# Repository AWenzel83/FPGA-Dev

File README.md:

# FPGA-Dev
Design and Supportfiles for the FPGA-Dev-Board used in the FPGA-Classes at the HS-Wismar

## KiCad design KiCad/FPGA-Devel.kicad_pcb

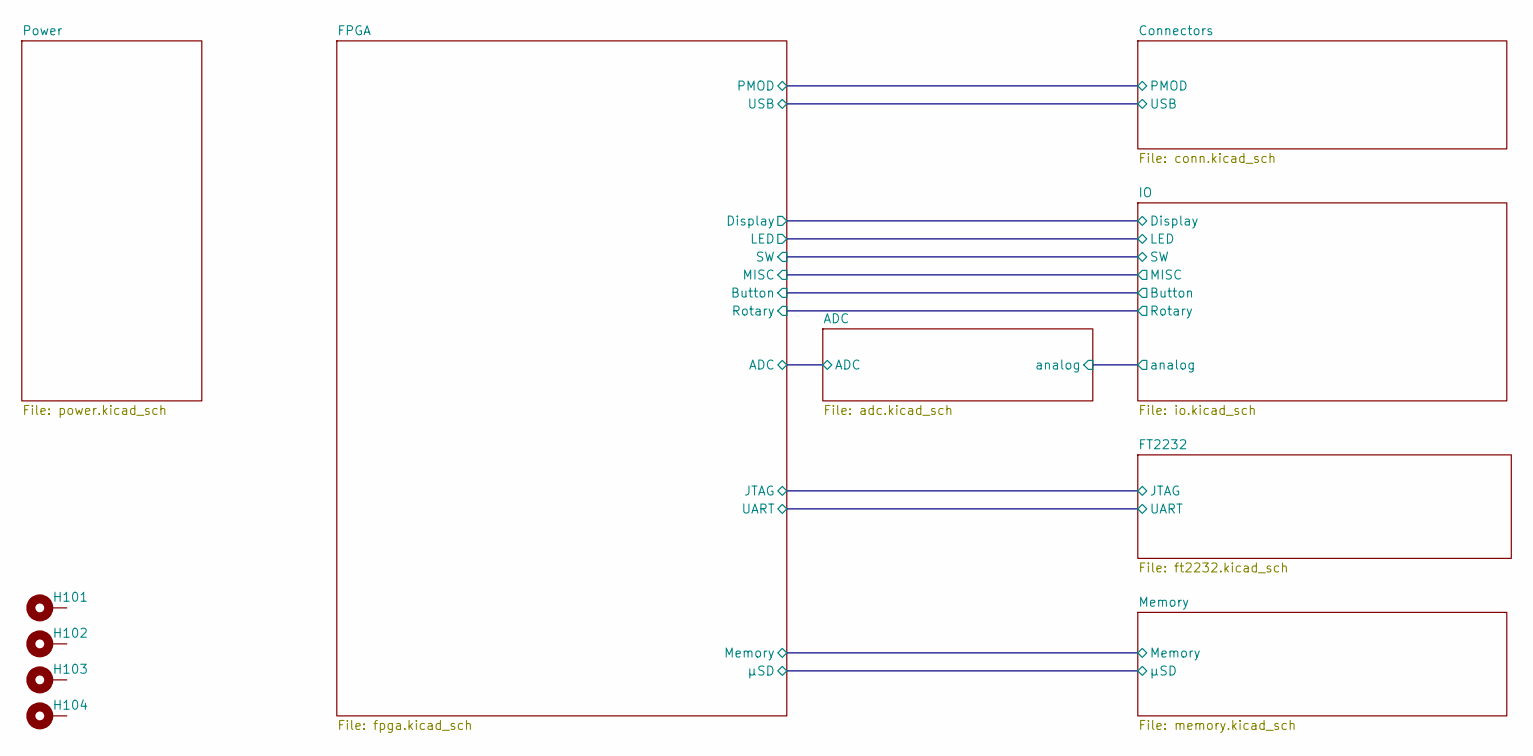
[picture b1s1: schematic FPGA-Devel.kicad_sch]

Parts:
H101, H102, H103, H104: MountingHole_Pad; MountingHole_3.2mm_M3_Pad_Via

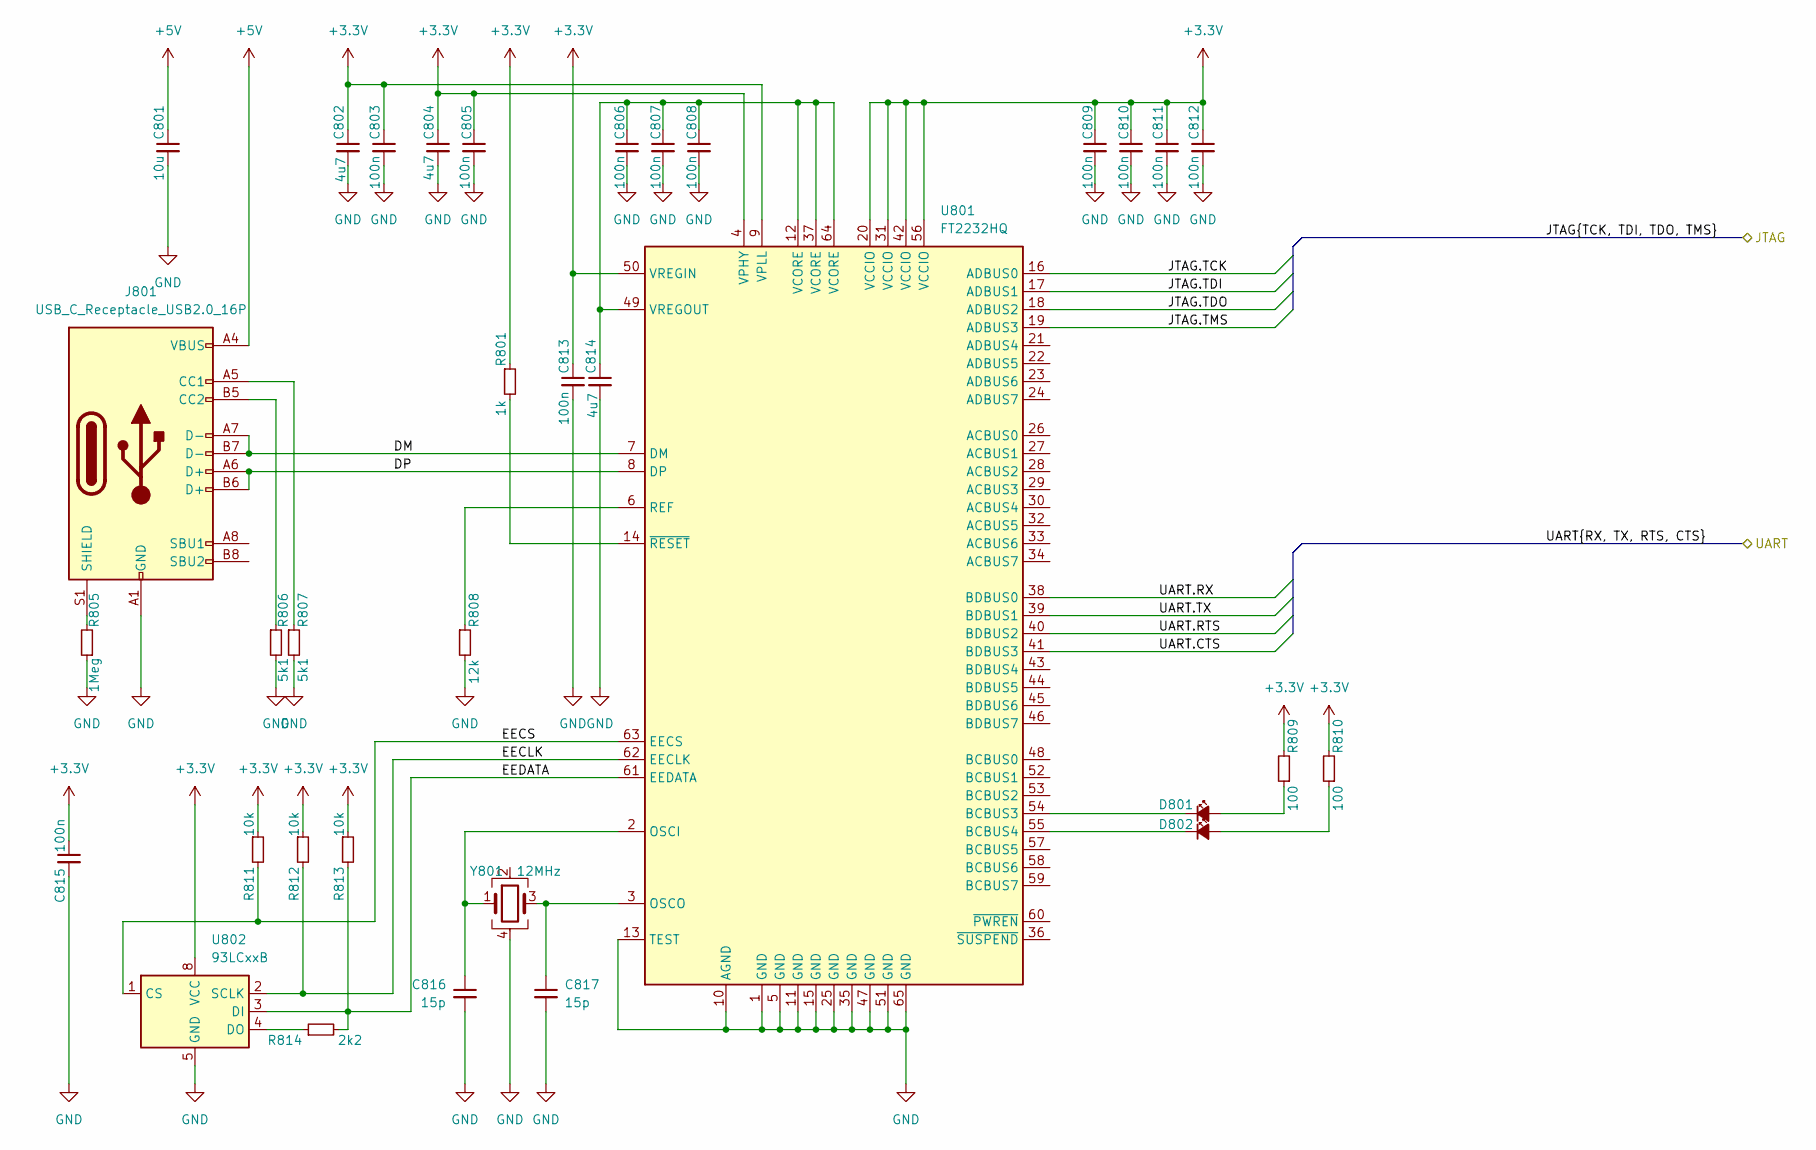
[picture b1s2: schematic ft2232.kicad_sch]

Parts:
C801: 10u; C_1206_3216Metric
C802, C804, C814: 4u7; C_0603_1608Metric
C803, C805, C806, C807, C808, C809, C810, C811, C812, C813, C815: 100n; C_0402_1005Metric
C816, C817: 15p; C_0402_1005Metric
D801, D802: LED_Small_Filled; LED_0603_1608Metric
J801: USB_C_Receptacle_USB2.0_16P; USB_C_Combo
R801: 1k; R_0402_1005Metric
R805: 1Meg; R_0402_1005Metric
R806, R807: 5k1; R_0402_1005Metric
R808: 12k; R_0402_1005Metric
R809, R810: 100; R_0402_1005Metric
R811, R812, R813: 10k; R_0402_1005Metric
R814: 2k2; R_0402_1005Metric
U801: FT2232HQ; QFN-64-1EP_9x9mm_P0.5mm_EP4.35x4.35mm
U802: 93LCxxB; SOIC-8_3.9x4.9mm_P1.27mm
Y801: 12MHz; Oscillator_SMD_Abracon_ASE-4Pin_3.2x2.5mm

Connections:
+3.3V: C802.1, C803.1, C804.1, C805.1, C809.1, C810.1, C811.1, C812.1, C813.1, C815.1, R801.1, R809.2, R810.2, R811.1, R812.1, R813.1, U801.4 (VPHY), U801.9 (VPLL), U801.20 (VCCIO), U801.31 (VCCIO), U801.42 (VCCIO), U801.50 (VREGIN), U801.56 (VCCIO), U802.8 (VCC); also elsewhere on the board
+5V: C801.1, J801.A4 (VBUS), J801.A9 (VBUS), J801.B4 (VBUS), J801.B9 (VBUS); also elsewhere on the board
/FT2232/DM: J801.A7 (D-), J801.B7 (D-), U801.7 (DM)
/FT2232/DP: J801.A6 (D+), J801.B6 (D+), U801.8 (DP)
/FT2232/EECLK: R812.2, U801.62 (EECLK), U802.2 (SCLK)
/FT2232/EECS: R811.2, U801.63 (EECS), U802.1 (CS)
/FT2232/EEDATA: R813.2, R814.2, U801.61 (EEDATA), U802.3 (DI)
/FT2232/JTAG.TCK: U801.16 (ADBUS0); also elsewhere on the board
/FT2232/JTAG.TDI: U801.17 (ADBUS1); also elsewhere on the board
/FT2232/JTAG.TDO: U801.18 (ADBUS2); also elsewhere on the board
/FT2232/JTAG.TMS: U801.19 (ADBUS3); also elsewhere on the board
/FT2232/UART.CTS: U801.41 (BDBUS3); also elsewhere on the board
/FT2232/UART.RTS: U801.40 (BDBUS2); also elsewhere on the board
/FT2232/UART.RX: U801.38 (BDBUS0); also elsewhere on the board
/FT2232/UART.TX: U801.39 (BDBUS1); also elsewhere on the board
GND: C801.2, C802.2, C803.2, C804.2, C805.2, C806.2, C807.2, C808.2, C809.2, C810.2, C811.2, C812.2, C813.2, C814.2, C815.2, C816.2, C817.2, J801.A1 (GND), J801.A12 (GND), J801.B1 (GND), J801.B12 (GND), R805.1, R806.2, R807.2, R808.2, U801.1 (GND), U801.5 (GND), U801.10 (AGND), U801.11 (GND), U801.13 (TEST), U801.15 (GND), U801.25 (GND), U801.35 (GND), U801.47 (GND), U801.51 (GND), U801.65 (GND), U802.5 (GND), Y801.4; also elsewhere on the board
unnamed: D801.2 (A), R809.1
unnamed: D801.1 (K), U801.54 (BCBUS3)
unnamed: D802.2 (A), R810.1
unnamed: D802.1 (K), U801.55 (BCBUS4)
unnamed: J801.A5 (CC1), R807.1
unnamed: J801.B5 (CC2), R806.1
unnamed: J801.S1 (SHIELD), R805.2
unnamed: C816.1, U801.2 (OSCI), Y801.1
unnamed: C817.1, U801.3 (OSCO), Y801.3
unnamed: R808.1, U801.6 (REF)
unnamed: C806.1, C807.1, C808.1, C814.1, U801.12 (VCORE), U801.37 (VCORE), U801.49 (VREGOUT), U801.64 (VCORE)
unnamed: R801.2, U801.14 (~RESET)
unnamed: R814.1, U802.4 (DO)

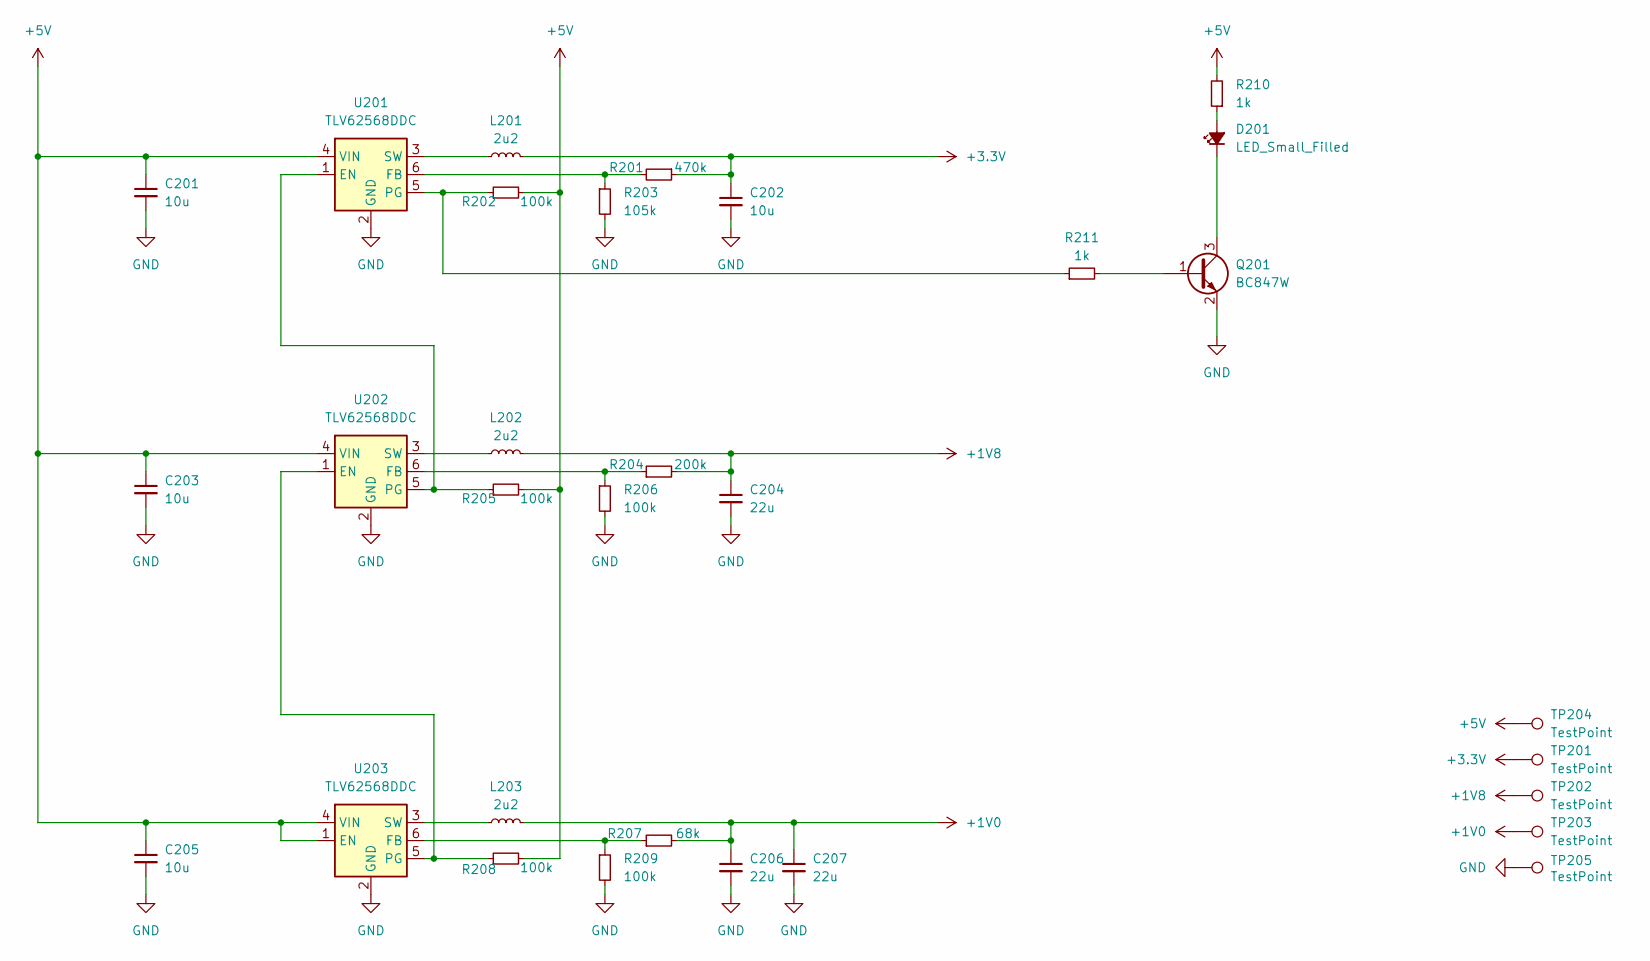
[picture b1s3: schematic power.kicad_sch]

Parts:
C201, C202, C203, C205: 10u; C_1206_3216Metric
C204, C206, C207: 22u; C_1206_3216Metric
D201: LED_Small_Filled; LED_0603_1608Metric
L201, L202, L203: 2u2; L_Bourns-SRN4018
Q201: BC847W; SOT-23-3
R201: 470k; R_0402_1005Metric
R202, R205, R206, R208, R209: 100k; R_0402_1005Metric
R203: 105k; R_0402_1005Metric
R204: 200k; R_0402_1005Metric
R207: 68k; R_0402_1005Metric
R210, R211: 1k; R_0402_1005Metric
TP201, TP202, TP203, TP204, TP205: TestPoint; TestPoint_THTPad_D2.0mm_Drill1.0mm
U201, U202, U203: TLV62568DDC; SOT-23-6

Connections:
+1V0: C206.1, C207.1, L203.2, R207.2, TP203.1 (1_1); also elsewhere on the board
+1V8: C204.1, L202.2, R204.2, TP202.1 (1_1); also elsewhere on the board
+3.3V: C202.1, L201.2, R201.1, TP201.1 (1_1); also elsewhere on the board
+5V: C201.1, C203.1, C205.1, R202.2, R205.2, R208.2, R210.2, TP204.1 (1_1), U201.4 (VIN), U202.4 (VIN), U203.1 (EN), U203.4 (VIN); also elsewhere on the board
GND: C201.2, C202.2, C203.2, C204.2, C205.2, C206.2, C207.2, Q201.2 (E), R203.2, R206.2, R209.2, TP205.1 (1_1), U201.2 (GND), U202.2 (GND), U203.2 (GND); also elsewhere on the board
unnamed: D201.2 (A), R210.1
unnamed: D201.1 (K), Q201.3 (C)
unnamed: Q201.1 (B), R211.2
unnamed: R205.1, U201.1 (EN), U202.5 (PG)
unnamed: R201.2, R203.1, U201.6 (FB)
unnamed: R202.1, R211.1, U201.5 (PG)
unnamed: L201.1, U201.3 (SW)
unnamed: R208.1, U202.1 (EN), U203.5 (PG)
unnamed: R204.1, R206.1, U202.6 (FB)
unnamed: L202.1, U202.3 (SW)
unnamed: R207.1, R209.1, U203.6 (FB)
unnamed: L203.1, U203.3 (SW)

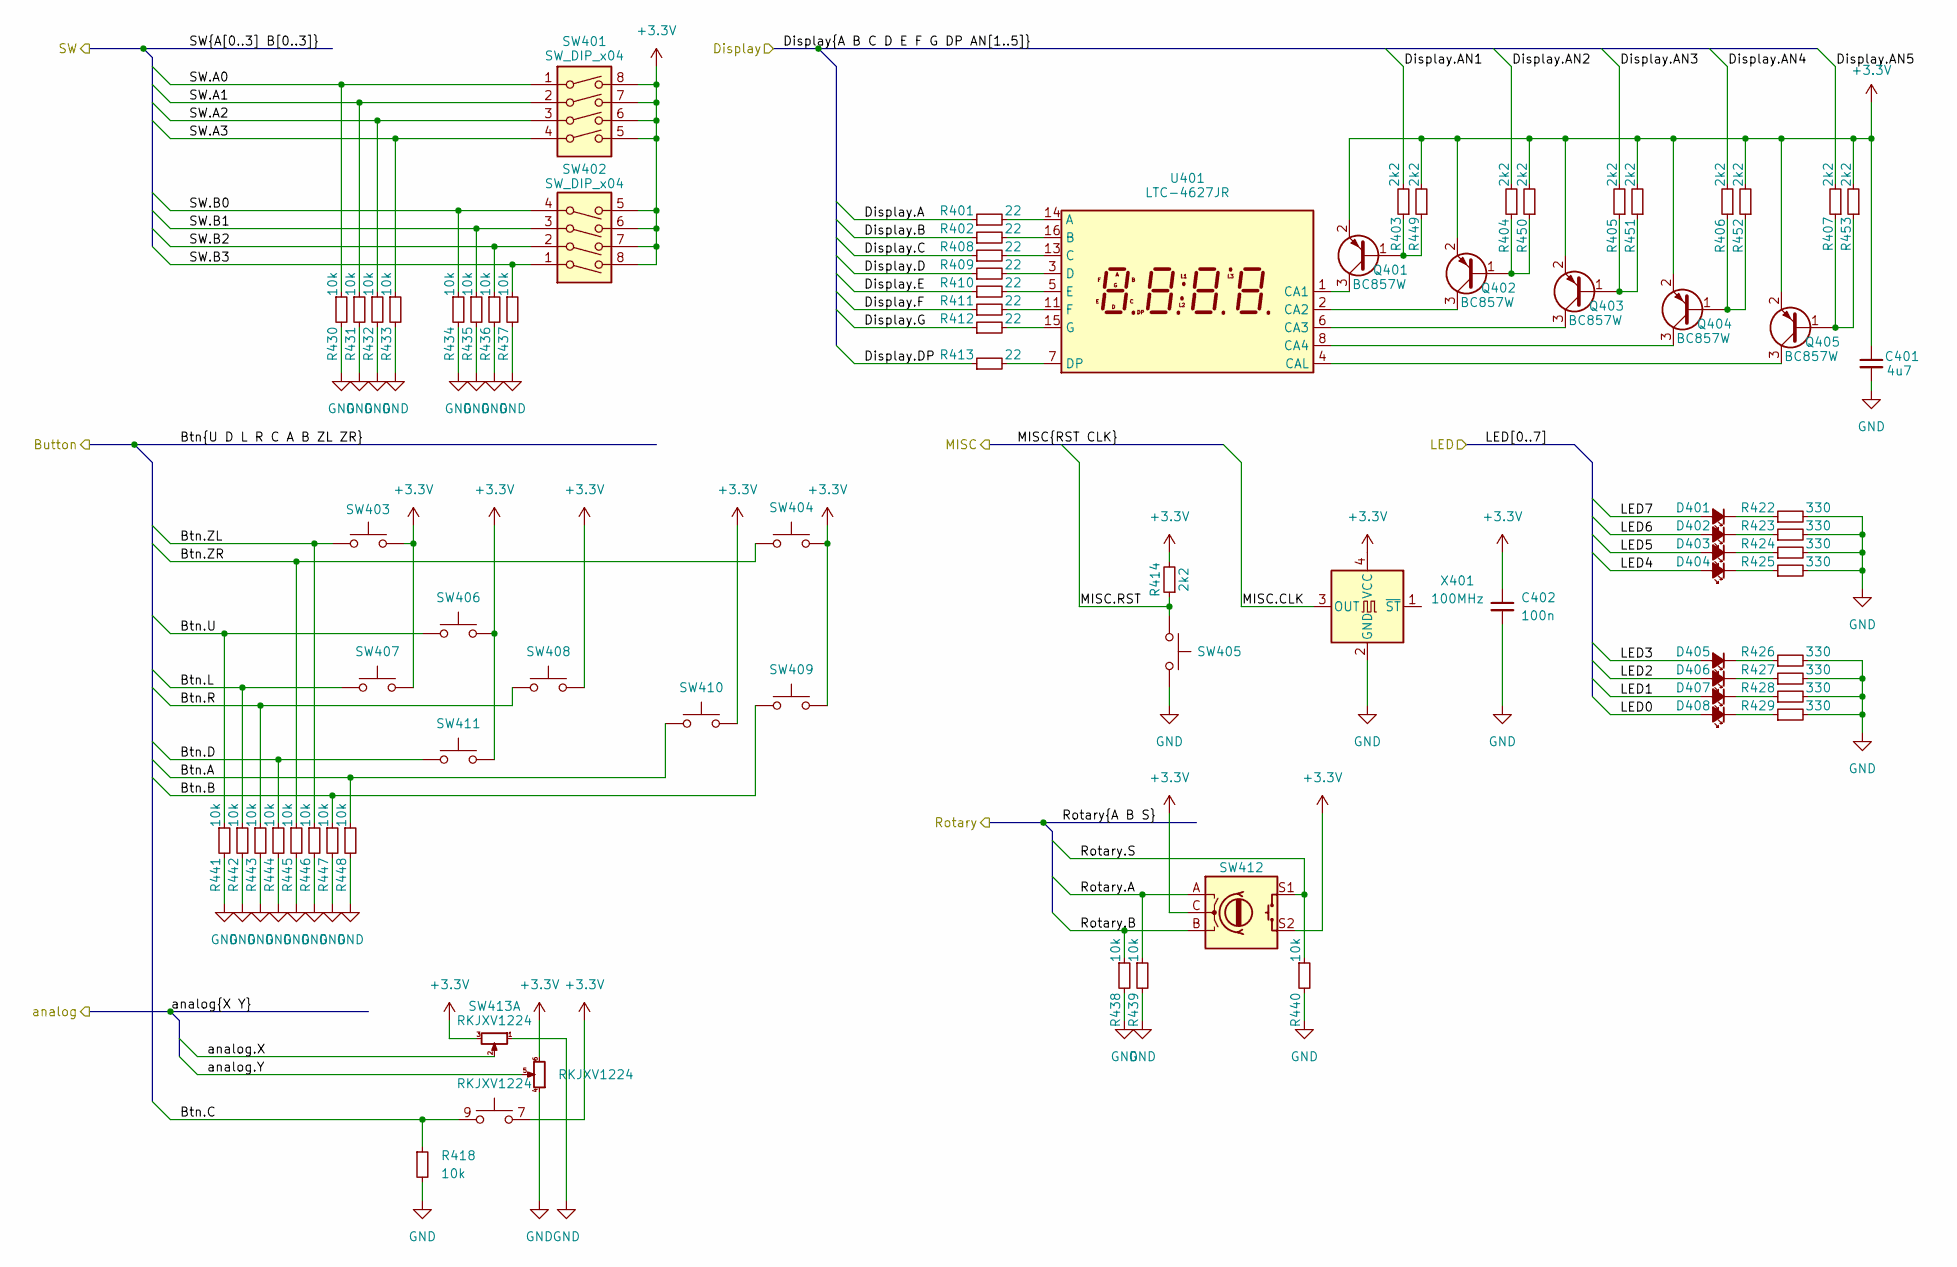
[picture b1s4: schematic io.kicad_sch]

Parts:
C401: 4u7; C_0603_1608Metric
C402: 100n; C_0402_1005Metric
D401, D402, D403, D404, D405, D406, D407, D408: LED_Small_Filled; LED_0603_1608Metric
Q401, Q402, Q403, Q404, Q405: BC857W; SOT-23-3
R401, R402, R408, R409, R410, R411, R412, R413: 22; R_0402_1005Metric
R403, R404, R405, R406, R407, R414, R449, R450, R451, R452, R453: 2k2; R_0402_1005Metric
R418, R430, R431, R432, R433, R434, R435, R436, R437, R438, R439, R440, R441, R442, R443, R444, R445, R446, R447, R448: 10k; R_0402_1005Metric
R422, R423, R424, R425, R426, R427, R428, R429: 330; R_0402_1005Metric
SW401, SW402: SW_DIP_x04; SW_DIP_SPSTx04_Slide_9.78x12.34mm_W7.62mm_P2.54mm
SW403, SW404: SW_Omron_B3FS; SW_Tactile_SPST_Angled_PTS645Vx39-2LFS
SW405, SW406, SW407, SW408, SW409, SW410, SW411: SW_Omron_B3FS; SW_PUSH_6mm_H4.3mm
SW412: RotaryEncoder_Switch; Alps_EC11E-Switch
SW413: RKJXV1224
U401: LTC-4627JR; LTC-4627Jx_compat
X401: 100MHz; Oscillator_SMD_Abracon_ASE-4Pin_3.2x2.5mm

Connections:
+3.3V: C401.1, C402.1, Q401.2 (E), Q402.2 (E), Q403.2 (E), Q404.2 (E), Q405.2 (E), R414.2, R449.2, R450.2, R451.2, R452.2, R453.2, SW401.5, SW401.6, SW401.7, SW401.8, SW402.5, SW402.6, SW402.7, SW402.8, SW403.2, SW404.1, SW406.2, SW407.2, SW408.2, SW409.2, SW410.2, SW411.2, SW412.C, SW412.S2, SW413.3, SW413.6, SW413.7 (A), SW413.8 (A), X401.4 (VCC); also elsewhere on the board
/ADC/analog.X: SW413.2; also elsewhere on the board
/ADC/analog.Y: SW413.5; also elsewhere on the board
/IO/Btn.A: R448.1, SW410.1; also elsewhere on the board
/IO/Btn.B: R447.1, SW409.1; also elsewhere on the board
/IO/Btn.C: R418.1, SW413.9 (B), SW413.10 (B); also elsewhere on the board
/IO/Btn.D: R444.1, SW411.1; also elsewhere on the board
/IO/Btn.L: R442.1, SW407.1; also elsewhere on the board
/IO/Btn.R: R443.1, SW408.1; also elsewhere on the board
/IO/Btn.U: R441.1, SW406.1; also elsewhere on the board
/IO/Btn.ZL: R446.1, SW403.1; also elsewhere on the board
/IO/Btn.ZR: R445.1, SW404.2; also elsewhere on the board
/IO/Display.A: R401.1; also elsewhere on the board
/IO/Display.AN1: R403.2; also elsewhere on the board
/IO/Display.AN2: R404.2; also elsewhere on the board
/IO/Display.AN3: R405.2; also elsewhere on the board
/IO/Display.AN4: R406.2; also elsewhere on the board
/IO/Display.AN5: R407.2; also elsewhere on the board
/IO/Display.B: R402.1; also elsewhere on the board
/IO/Display.C: R408.1; also elsewhere on the board
/IO/Display.D: R409.1; also elsewhere on the board
/IO/Display.DP: R413.1; also elsewhere on the board
/IO/Display.E: R410.1; also elsewhere on the board
/IO/Display.F: R411.1; also elsewhere on the board
/IO/Display.G: R412.1; also elsewhere on the board
/IO/LED0: D408.2 (A); also elsewhere on the board
/IO/LED1: D407.2 (A); also elsewhere on the board
/IO/LED2: D406.2 (A); also elsewhere on the board
/IO/LED3: D405.2 (A); also elsewhere on the board
/IO/LED4: D404.2 (A); also elsewhere on the board
/IO/LED5: D403.2 (A); also elsewhere on the board
/IO/LED6: D402.2 (A); also elsewhere on the board
/IO/LED7: D401.2 (A); also elsewhere on the board
/IO/MISC.CLK: X401.3 (OUT); also elsewhere on the board
/IO/MISC.RST: R414.1, SW405.1; also elsewhere on the board
/IO/Rotary.A: R439.1, SW412.A; also elsewhere on the board
/IO/Rotary.B: R438.1, SW412.B; also elsewhere on the board
/IO/Rotary.S: R440.1, SW412.S1; also elsewhere on the board
/IO/SW.A0: R430.1, SW401.1; also elsewhere on the board
/IO/SW.A1: R431.1, SW401.2; also elsewhere on the board
/IO/SW.A2: R432.1, SW401.3; also elsewhere on the board
/IO/SW.A3: R433.1, SW401.4; also elsewhere on the board
/IO/SW.B0: R434.1, SW402.4; also elsewhere on the board
/IO/SW.B1: R435.1, SW402.3; also elsewhere on the board
/IO/SW.B2: R436.1, SW402.2; also elsewhere on the board
/IO/SW.B3: R437.1, SW402.1; also elsewhere on the board
GND: C401.2, C402.2, R418.2, R422.2, R423.2, R424.2, R425.2, R426.2, R427.2, R428.2, R429.2, R430.2, R431.2, R432.2, R433.2, R434.2, R435.2, R436.2, R437.2, R438.2, R439.2, R440.2, R441.2, R442.2, R443.2, R444.2, R445.2, R446.2, R447.2, R448.2, SW405.2, SW413.1, SW413.4, X401.2 (GND); also elsewhere on the board
unnamed: D401.1 (K), R422.1
unnamed: D402.1 (K), R423.1
unnamed: D403.1 (K), R424.1
unnamed: D404.1 (K), R425.1
unnamed: D405.1 (K), R426.1
unnamed: D406.1 (K), R427.1
unnamed: D407.1 (K), R428.1
unnamed: D408.1 (K), R429.1
unnamed: Q401.1 (B), R403.1, R449.1
unnamed: Q401.3 (C), U401.1 (CA1)
unnamed: Q402.1 (B), R404.1, R450.1
unnamed: Q402.3 (C), U401.2 (CA2)
unnamed: Q403.1 (B), R405.1, R451.1
unnamed: Q403.3 (C), U401.6 (CA3)
unnamed: Q404.1 (B), R406.1, R452.1
unnamed: Q404.3 (C), U401.8 (CA4)
unnamed: Q405.1 (B), R407.1, R453.1
unnamed: Q405.3 (C), U401.4 (CAL)
unnamed: R401.2, U401.14 (A)
unnamed: R402.2, U401.16 (B)
unnamed: R408.2, U401.13 (C)
unnamed: R409.2, U401.3 (D)
unnamed: R413.2, U401.7 (DP)
unnamed: R410.2, U401.5 (E)
unnamed: R411.2, U401.11 (F)
unnamed: R412.2, U401.15 (G)

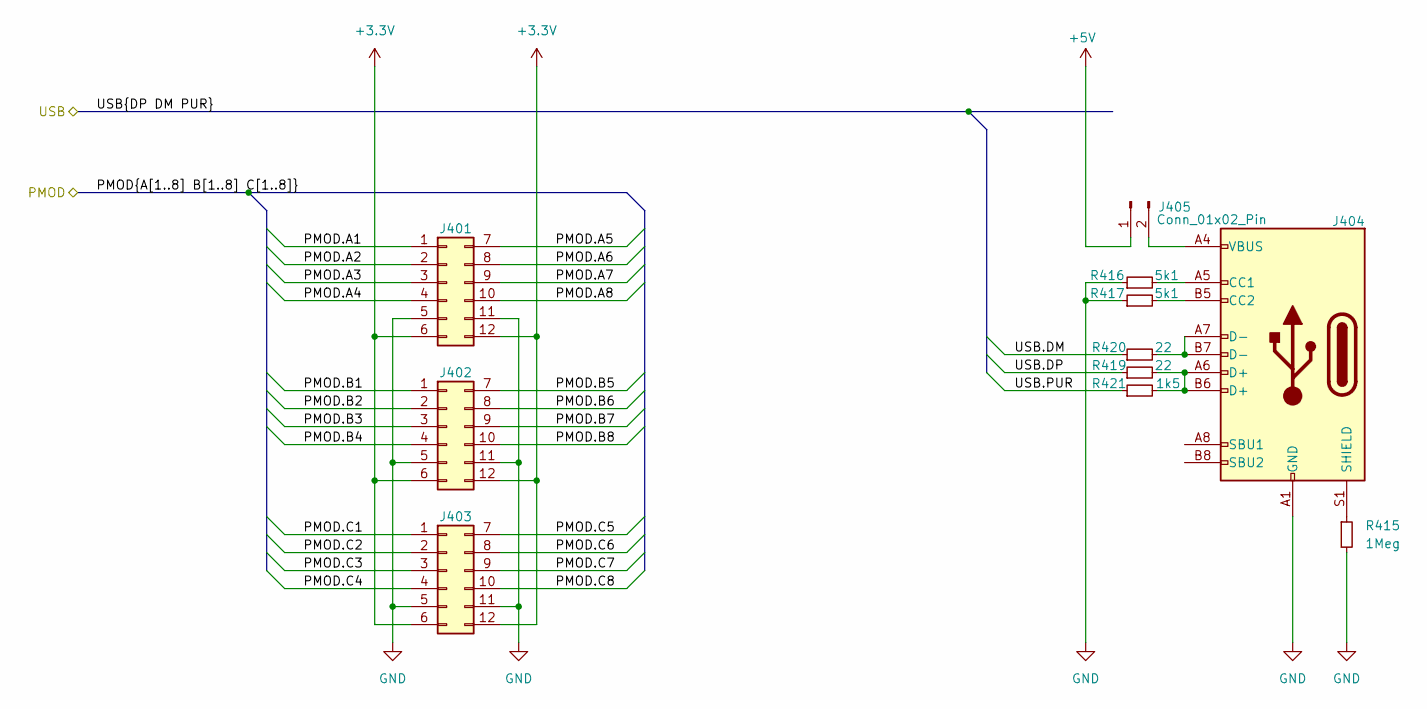
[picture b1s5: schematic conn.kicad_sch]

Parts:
J401, J402, J403: Conn_02x06_Top_Bottom; PMOD
J404: USB_C_Receptacle_USB2.0_16P; USB_C_Combo
J405: Conn_01x02_Pin; PinHeader_1x02_P2.54mm_Horizontal
R415: 1Meg; R_0402_1005Metric
R416, R417: 5k1; R_0402_1005Metric
R419, R420: 22; R_0402_1005Metric
R421: 1k5; R_0402_1005Metric

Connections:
+3.3V: J401.6, J401.12, J402.6, J402.12, J403.6, J403.12; also elsewhere on the board
+5V: J405.1; also elsewhere on the board
/Connectors/PMOD.A1: J401.1; also elsewhere on the board
/Connectors/PMOD.A2: J401.2; also elsewhere on the board
/Connectors/PMOD.A3: J401.3; also elsewhere on the board
/Connectors/PMOD.A4: J401.4; also elsewhere on the board
/Connectors/PMOD.A5: J401.7; also elsewhere on the board
/Connectors/PMOD.A6: J401.8; also elsewhere on the board
/Connectors/PMOD.A7: J401.9; also elsewhere on the board
/Connectors/PMOD.A8: J401.10; also elsewhere on the board
/Connectors/PMOD.B1: J402.1; also elsewhere on the board
/Connectors/PMOD.B2: J402.2; also elsewhere on the board
/Connectors/PMOD.B3: J402.3; also elsewhere on the board
/Connectors/PMOD.B4: J402.4; also elsewhere on the board
/Connectors/PMOD.B5: J402.7; also elsewhere on the board
/Connectors/PMOD.B6: J402.8; also elsewhere on the board
/Connectors/PMOD.B7: J402.9; also elsewhere on the board
/Connectors/PMOD.B8: J402.10; also elsewhere on the board
/Connectors/PMOD.C1: J403.1; also elsewhere on the board
/Connectors/PMOD.C2: J403.2; also elsewhere on the board
/Connectors/PMOD.C3: J403.3; also elsewhere on the board
/Connectors/PMOD.C4: J403.4; also elsewhere on the board
/Connectors/PMOD.C5: J403.7; also elsewhere on the board
/Connectors/PMOD.C6: J403.8; also elsewhere on the board
/Connectors/PMOD.C7: J403.9; also elsewhere on the board
/Connectors/PMOD.C8: J403.10; also elsewhere on the board
/Connectors/USB.DM: R420.1; also elsewhere on the board
/Connectors/USB.DP: R419.1; also elsewhere on the board
/Connectors/USB.PUR: R421.1; also elsewhere on the board
GND: J401.5, J401.11, J402.5, J402.11, J403.5, J403.11, J404.A1 (GND), J404.A12 (GND), J404.B1 (GND), J404.B12 (GND), R415.2, R416.1, R417.1; also elsewhere on the board
unnamed: J404.A5 (CC1), R416.2
unnamed: J404.B5 (CC2), R417.2
unnamed: J404.A6 (D+), J404.B6 (D+), R419.2, R421.2
unnamed: J404.A7 (D-), J404.B7 (D-), R420.2
unnamed: J404.S1 (SHIELD), R415.1
unnamed: J404.A4 (VBUS), J404.A9 (VBUS), J404.B4 (VBUS), J404.B9 (VBUS), J405.2

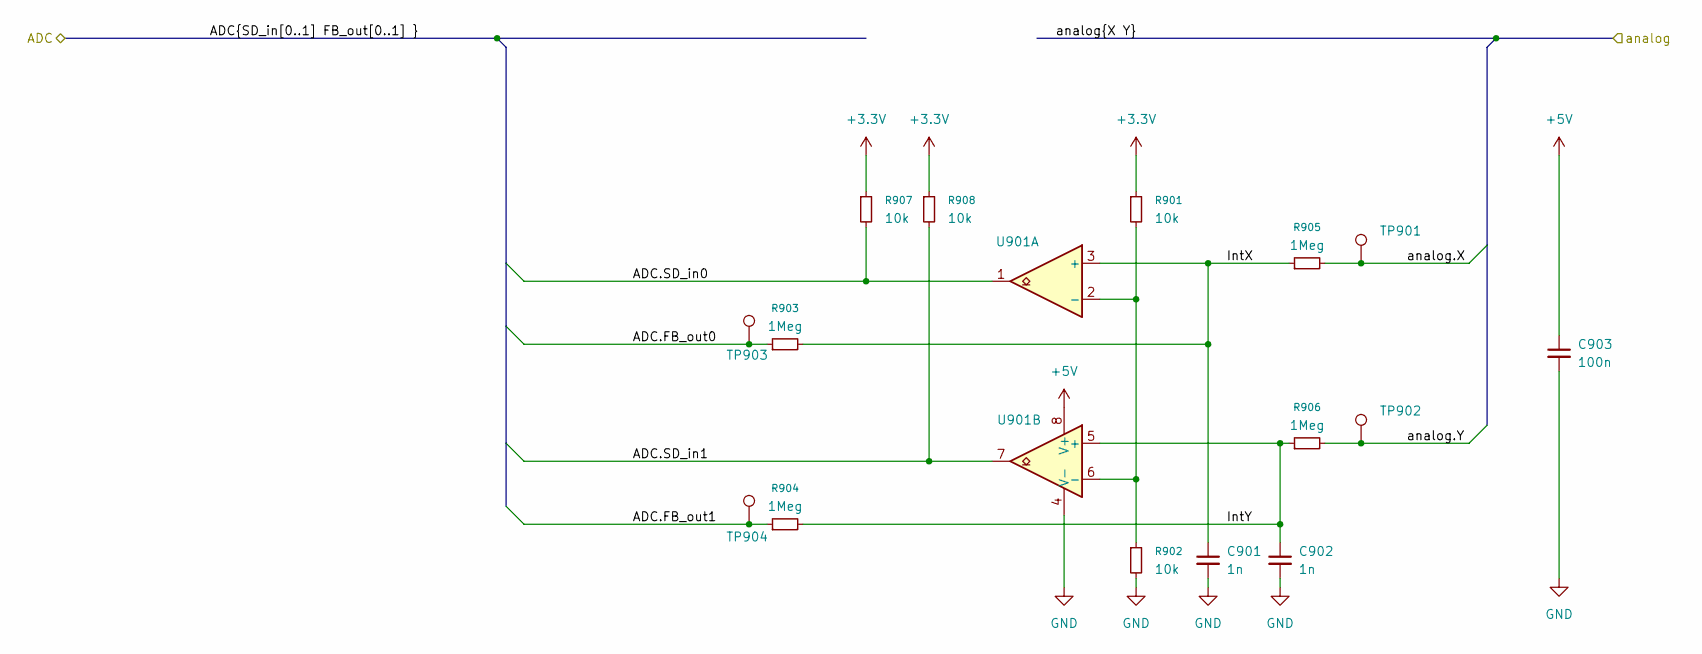
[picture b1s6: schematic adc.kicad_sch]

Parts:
C901, C902: 1n; C_0402_1005Metric
C903: 100n; C_0402_1005Metric
R901, R902, R907, R908: 10k; R_0402_1005Metric
R903, R904, R905, R906: 1Meg; R_0402_1005Metric
TP901, TP902, TP903, TP904: TestPoint; TestPoint_THTPad_D2.0mm_Drill1.0mm
U901: LM2903; VSSOP-8_3x3mm_P0.65mm

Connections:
+3.3V: R901.1, R907.1, R908.1; also elsewhere on the board
+5V: C903.1, U901.8 (V+); also elsewhere on the board
/ADC/ADC.FB_out0: R903.1, TP903.1 (1_1); also elsewhere on the board
/ADC/ADC.FB_out1: R904.1, TP904.1 (1_1); also elsewhere on the board
/ADC/ADC.SD_in0: R907.2, U901.1; also elsewhere on the board
/ADC/ADC.SD_in1: R908.2, U901.7; also elsewhere on the board
/ADC/IntX: C901.1, R903.2, R905.1, U901.3 (+)
/ADC/IntY: C902.1, R904.2, R906.1, U901.5 (+)
/ADC/analog.X: R905.2, TP901.1 (1_1); also elsewhere on the board
/ADC/analog.Y: R906.2, TP902.1 (1_1); also elsewhere on the board
GND: C901.2, C902.2, C903.2, R902.2, U901.4 (V-); also elsewhere on the board
unnamed: R901.2, R902.1, U901.2 (-), U901.6 (-)

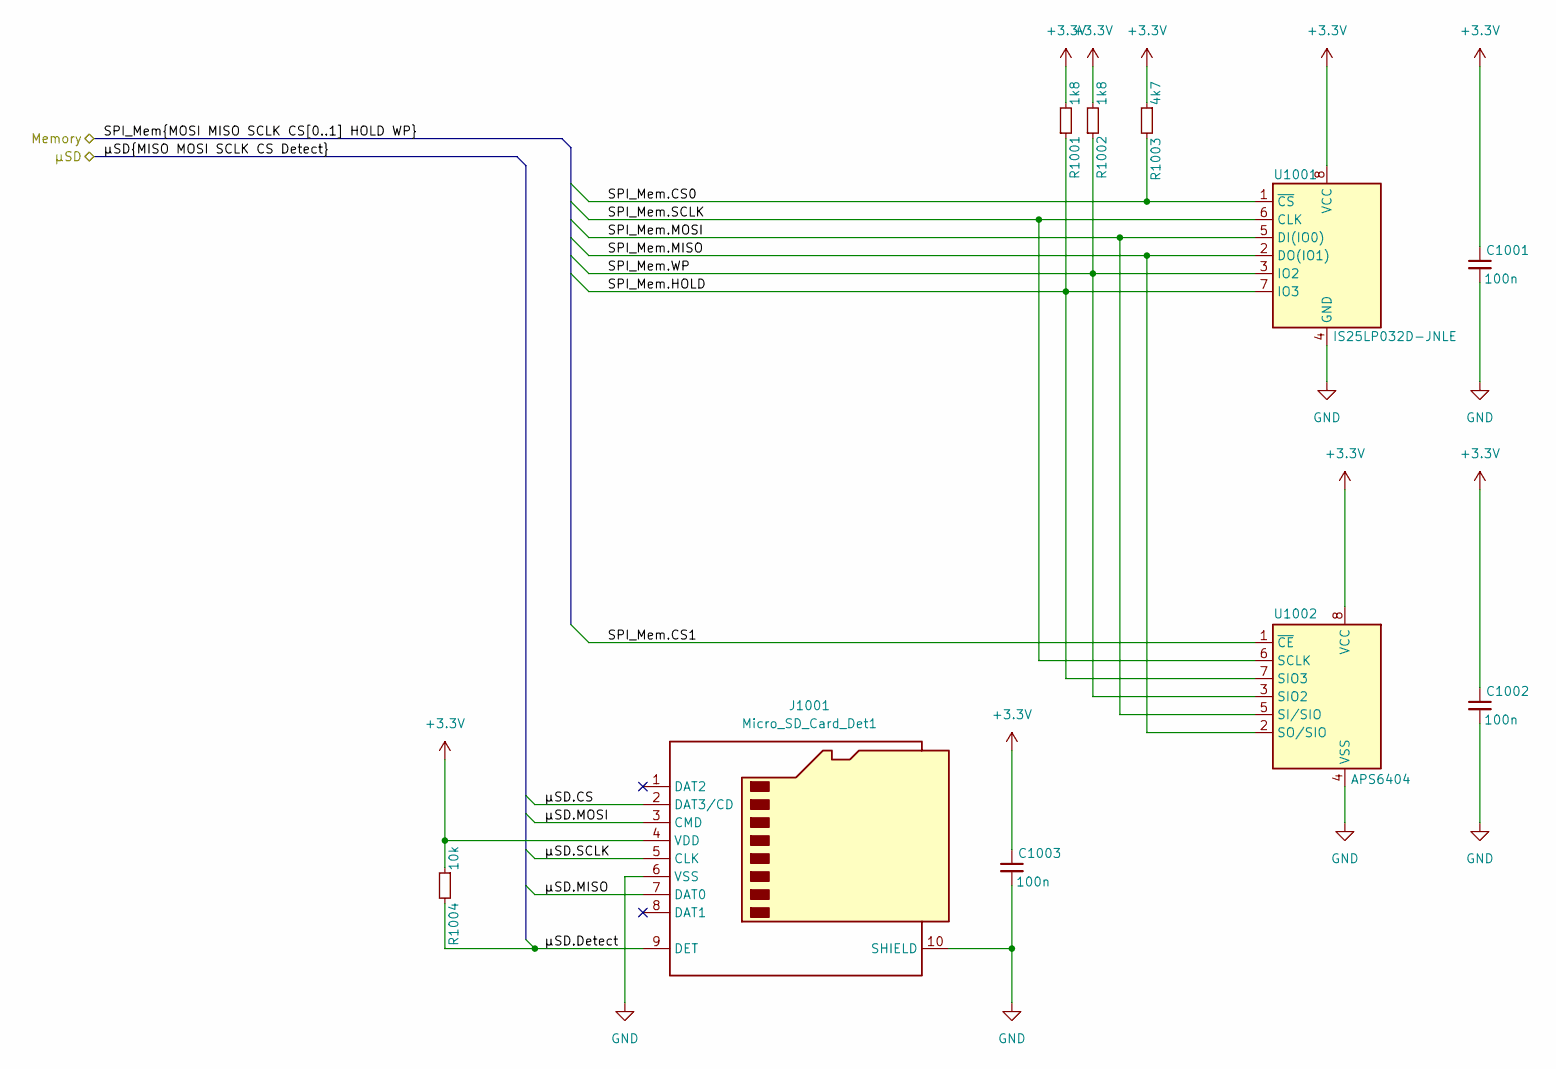
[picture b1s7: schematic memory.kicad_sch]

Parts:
C1001, C1002, C1003: 100n; C_0402_1005Metric
J1001: Micro_SD_Card_Det1; microSD_Wuerth_693071010811
R1001, R1002: 1k8; R_0402_1005Metric
R1003: 4k7; R_0402_1005Metric
R1004: 10k; R_0402_1005Metric
U1001: IS25LP032D-JNLE; SOIC-8_4_5.3_combo_P1.27mm
U1002: APS6404; SOIC-8_3.9x4.9mm_P1.27mm

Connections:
+3.3V: C1001.1, C1002.1, C1003.1, J1001.4 (VDD), R1001.2, R1002.2, R1003.1, R1004.1, U1001.8 (VCC), U1002.8 (VCC); also elsewhere on the board
/Memory/SPI_Mem.CS0: R1003.2, U1001.1 (~CS); also elsewhere on the board
/Memory/SPI_Mem.CS1: U1002.1 (~CE); also elsewhere on the board
/Memory/SPI_Mem.HOLD: R1001.1, U1001.7 (IO3), U1002.7 (SIO3); also elsewhere on the board
/Memory/SPI_Mem.MISO: U1001.2 (DO(IO1)), U1002.2 (SO/SIO); also elsewhere on the board
/Memory/SPI_Mem.MOSI: U1001.5 (DI(IO0)), U1002.5 (SI/SIO); also elsewhere on the board
/Memory/SPI_Mem.SCLK: U1001.6 (CLK), U1002.6 (SCLK); also elsewhere on the board
/Memory/SPI_Mem.WP: R1002.1, U1001.3 (IO2), U1002.3 (SIO2); also elsewhere on the board
/Memory/μSD.CS: J1001.2 (DAT3/CD); also elsewhere on the board
/Memory/μSD.Detect: J1001.9 (DET), R1004.2; also elsewhere on the board
/Memory/μSD.MISO: J1001.7 (DAT0); also elsewhere on the board
/Memory/μSD.MOSI: J1001.3 (CMD); also elsewhere on the board
/Memory/μSD.SCLK: J1001.5 (CLK); also elsewhere on the board
GND: C1001.2, C1002.2, C1003.2, J1001.6 (VSS), J1001.10 (SHIELD), U1001.4 (GND), U1002.4 (VSS); also elsewhere on the board

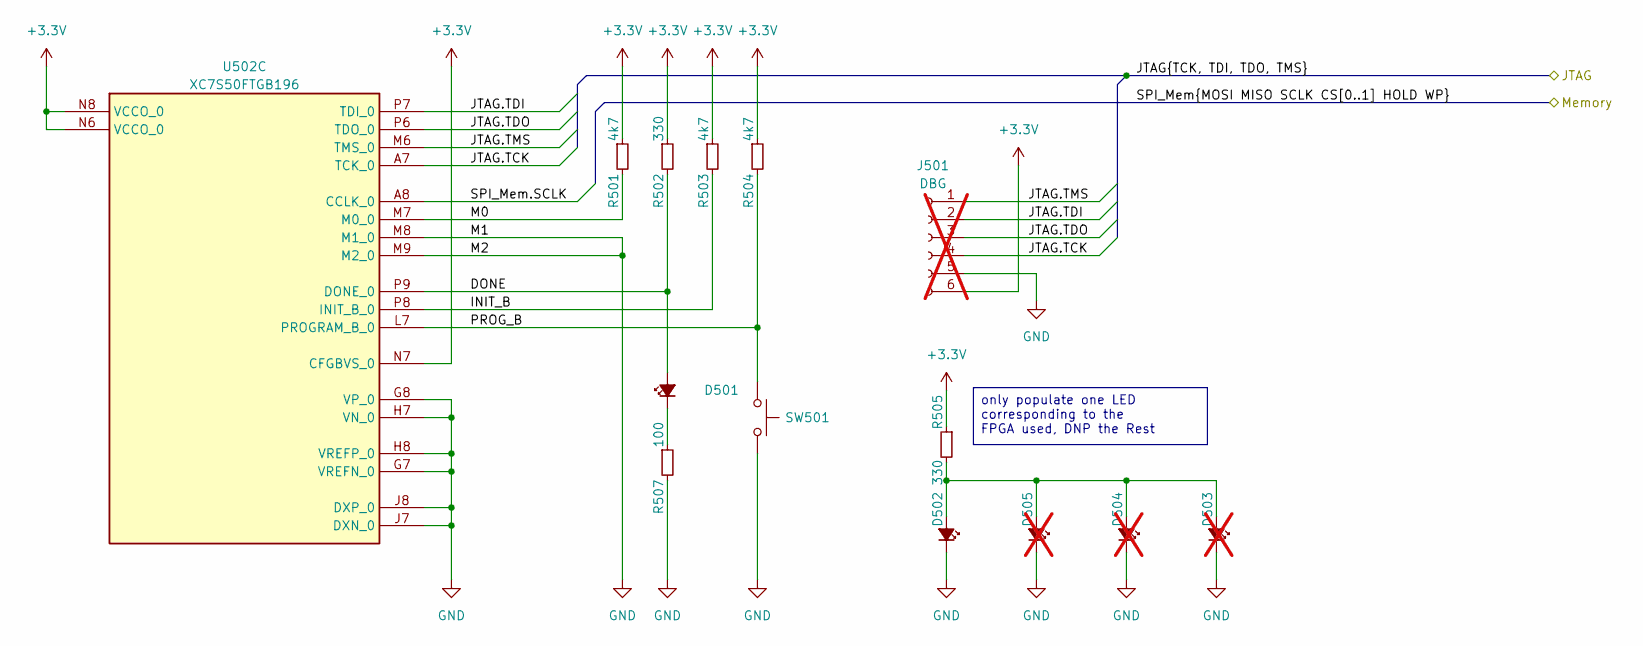
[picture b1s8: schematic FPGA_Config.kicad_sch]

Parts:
D501: LED_Small_Filled; LED_0603_1608Metric
D502: LED_Small_Filled; LED_0603_1608Metric_Box
D503, D504, D505: LED_Small_Filled; LED_0603_1608Metric_Box; not fitted
J501: DBG; PinHeader_1x06_P2.54mm_Vertical_versetzt; not fitted
R501, R503, R504: 4k7; R_0402_1005Metric
R502, R505: 330; R_0402_1005Metric
R507: 100; R_0402_1005Metric
SW501: SW_Omron_B3FS; SW_PUSH_6mm_H4.3mm
U502: XC7S50FTGB196; Xilinx_FTGB196

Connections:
+3.3V: J501.6, R501.1, R502.1, R503.1, R504.1, R505.1, U502.N6 (VCCO_0), U502.N7 (CFGBVS_0), U502.N8 (VCCO_0); also elsewhere on the board
/FPGA/FPGA_Config/DONE: D501.2 (A), R502.2, U502.P9 (DONE_0)
/FPGA/FPGA_Config/INIT_B: R503.2, U502.P8 (INIT_B_0)
/FPGA/FPGA_Config/M0: R501.2, U502.M7 (M0_0)
/FPGA/FPGA_Config/PROG_B: R504.2, SW501.1, U502.L7 (PROGRAM_B_0)
/FT2232/JTAG.TCK: J501.4, U502.A7 (TCK_0); also elsewhere on the board
/FT2232/JTAG.TDI: J501.2, U502.P7 (TDI_0); also elsewhere on the board
/FT2232/JTAG.TDO: J501.3, U502.P6 (TDO_0); also elsewhere on the board
/FT2232/JTAG.TMS: J501.1, U502.M6 (TMS_0); also elsewhere on the board
/Memory/SPI_Mem.SCLK: U502.A8 (CCLK_0); also elsewhere on the board
GND: D502.1 (K), D503.1 (K), D504.1 (K), D505.1 (K), J501.5, R507.2, SW501.2, U502.G7 (VREFN_0), U502.G8 (VP_0), U502.H7 (VN_0), U502.H8 (VREFP_0), U502.J7 (DXN_0), U502.J8 (DXP_0), U502.M8 (M1_0), U502.M9 (M2_0); also elsewhere on the board
unnamed: D501.1 (K), R507.1
unnamed: D502.2 (A), D503.2 (A), D504.2 (A), D505.2 (A), R505.2

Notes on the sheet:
only populate one LED corresponding to the FPGA used, DNP the Rest
